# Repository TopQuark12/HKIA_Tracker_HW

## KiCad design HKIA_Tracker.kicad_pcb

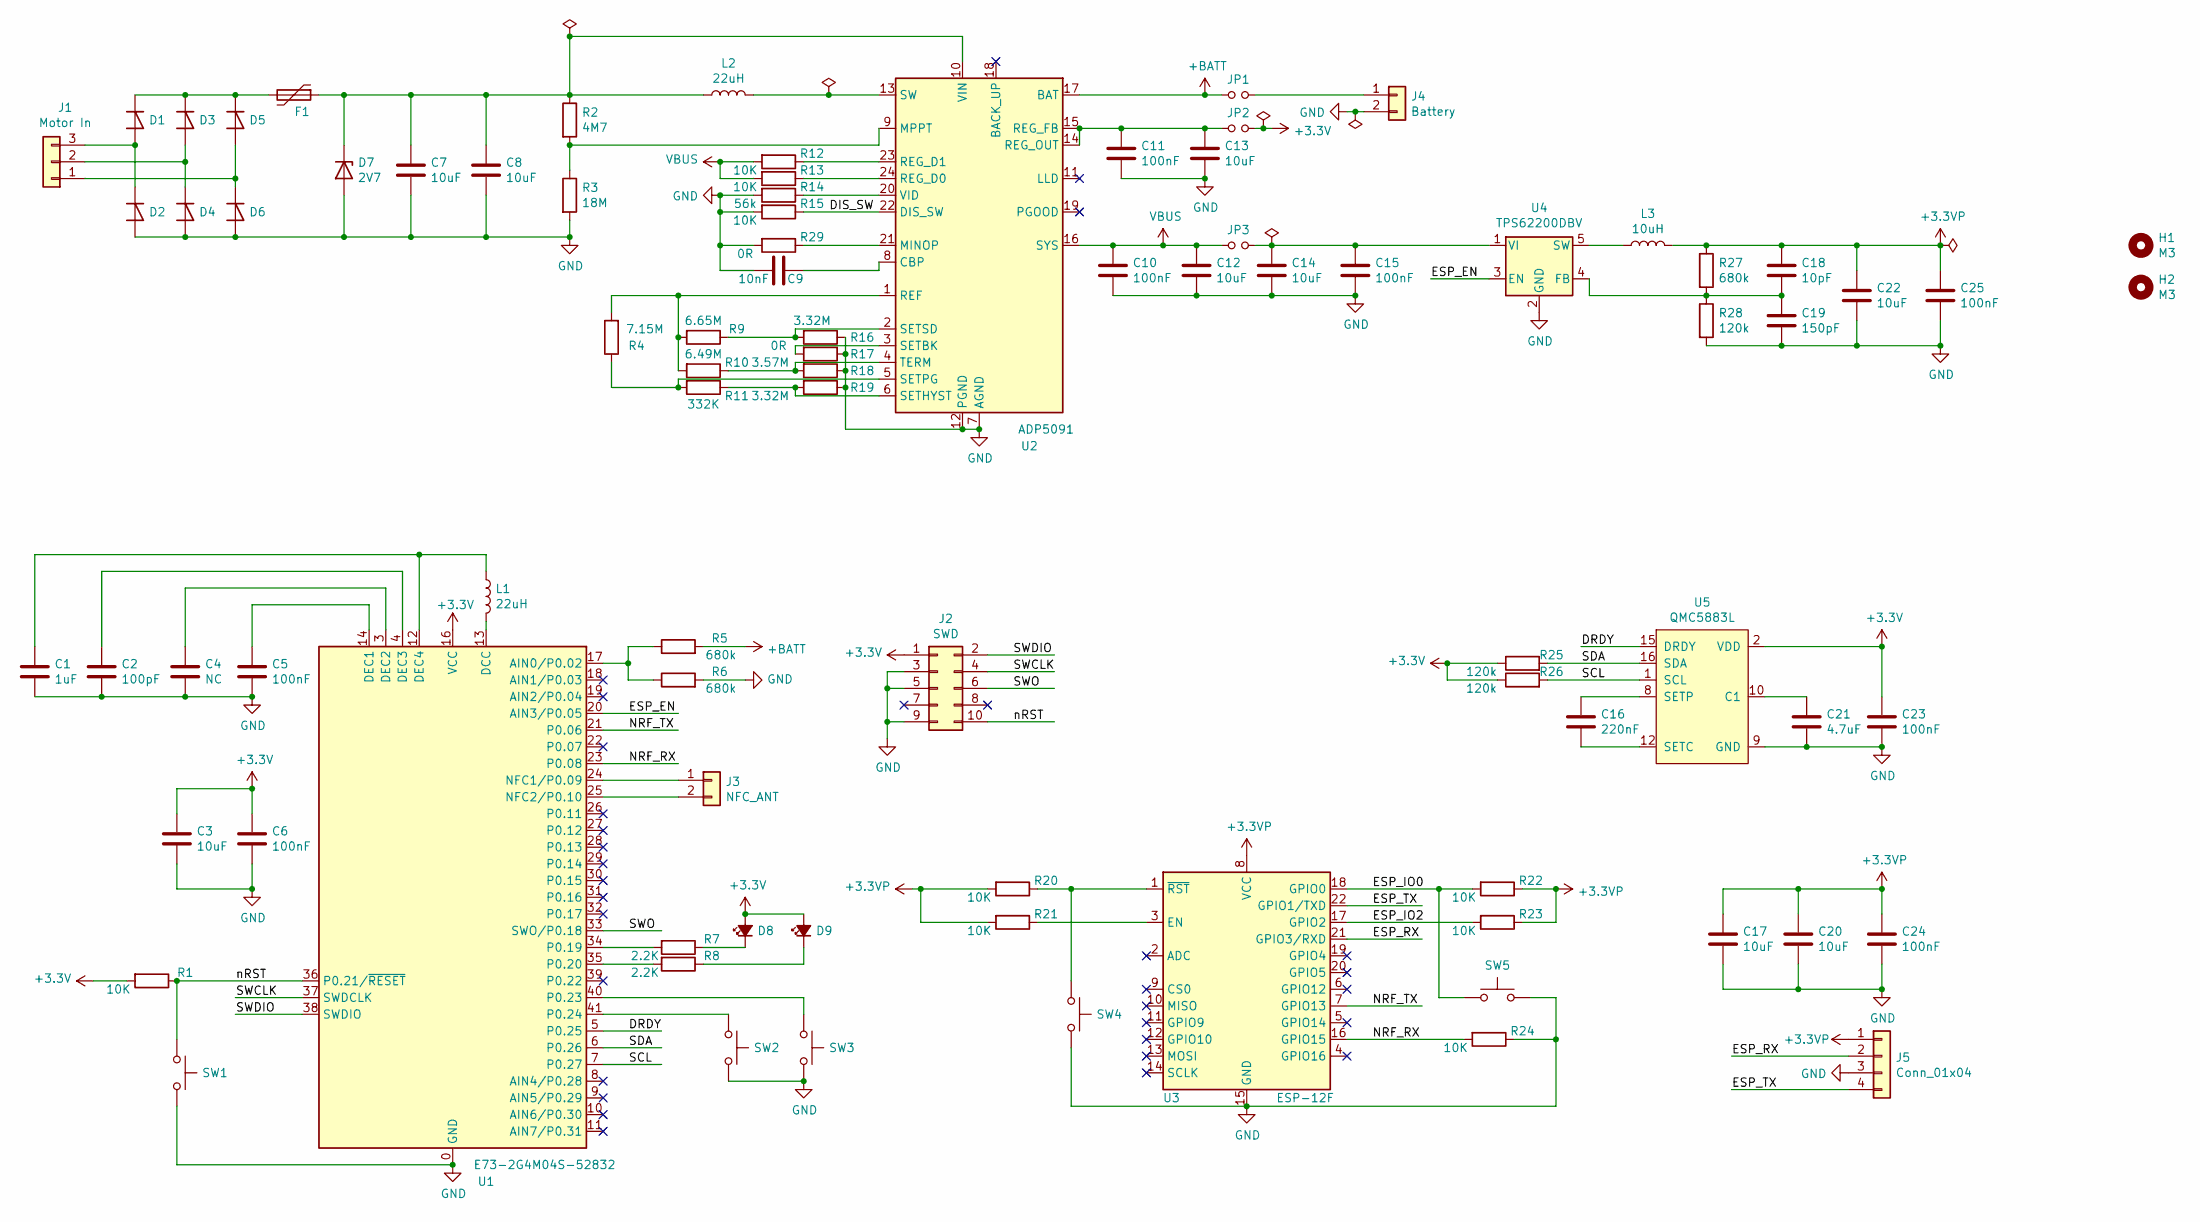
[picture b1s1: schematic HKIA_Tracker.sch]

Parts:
C1: 1uF; C_0603_1608Metric; LCSC C105174
C2: 100pF; C_0603_1608Metric; LCSC C14665
C3, C7, C8, C12, C13, C14, C17, C20, C22: 10uF; C_0805_2012Metric; LCSC C95841
C4: NC; C_0603_1608Metric
C5, C6, C10, C11, C15, C23, C24, C25: 100nF; C_0603_1608Metric; LCSC C1591
C9: 10nF; C_0603_1608Metric; LCSC C76710
C16: 220nF; C_0603_1608Metric; LCSC C83626
C18: 10pF; C_0603_1608Metric; LCSC C106245
C19: 150pF; C_0603_1608Metric; LCSC C107038
C21: 4.7uF; C_0603_1608Metric; LCSC C108342
D1, D2, D3, D4, D5, D6: 15MQ060N; D_SMA; LCSC C260222
D7: 2V7; SOT-223; DIGI 1727-5570-1-ND
D8, D9: LED_Small_ALT; D_0603_1608Metric; LCSC C72043
F1: MF-NSMF035X-2; R_1206_3216Metric; LCSC C208468
H1, H2: M3; MountingHole_3.2mm_M3_Pad
J1: Motor In; PinHeader_1x03_P2.54mm_Vertical
J2: SWD; PinHeader_2x05_P1.27mm_Vertical_SMD
J3: NFC_ANT; PinHeader_1x02_P2.54mm_Vertical
J4: Battery; JST_PH_S2B-PH-SM4-TB_1x02-1MP_P2.00mm_Horizontal; LCSC C132500
J5: Conn_01x04; PinHeader_1x04_P2.54mm_Vertical
JP1, JP2, JP3: Jumper_NO_Small; SolderJumper-2_P1.3mm_Open_RoundedPad1.0x1.5mm
L1, L2: 22uH; L_1210_3225Metric; LCSC C223225
L3: 10uH; L_1210_3225Metric; LCSC C21764
R1, R12, R13, R15, R20, R21, R22, R23, R24: 10K; R_0603_1608Metric; LCSC C98220
R2: 4M7; R_0603_1608Metric; LCSC C170740
R3: 18M; R_0603_1608Metric; LCSC C407494
R4: 7.15M; R_0603_1608Metric; LCSC C482906
R5, R6, R27: 680k; R_0603_1608Metric; LCSC C25822
R7, R8: 2.2K; R_0603_1608Metric; LCSC C25992
R9: 6.65M; R_0603_1608Metric; LCSC C228029
R10: 6.49M; R_0603_1608Metric; LCSC C482895
R11: 332K; R_0603_1608Metric; LCSC C23139
R14: 56k; R_0603_1608Metric; LCSC C304766
R16, R19: 3.32M; R_0603_1608Metric; LCSC C422938
R17, R29: 0R; R_0603_1608Metric; LCSC C15402
R18: 3.57M; R_0603_1608Metric; LCSC C367747
R25, R26, R28: 120k; R_0603_1608Metric; LCSC C203266
SW1, SW2, SW3, SW4, SW5: SW_Push; SW_SPST_CK_KXT3; LCSC C221821
U1: E73-2G4M04S-52832; E73-2G4M04S
U2: ADP5091; LFCSP-24-1EP_4x4mm_P0.5mm_EP2.3x2.3mm
U3: ESP-12F; ESP-12E
U4: TPS62200DBV; SOT-23-5
U5: QMC5883L; LGA-16_3x3mm_P0.5mm

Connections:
+3.3VP: C17.1, C18.1, C20.1, C22.1, C24.1, C25.1, J5.1, L3.2, R20.2, R21.2, R22.1, R23.1, R27.1, U3.8 (VCC)
+3V3: C3.1, C6.1, C23.1, D8.2 (A), D9.2 (A), J2.1, JP2.2, R1.2, R25.1, R26.1, U1.16 (VCC), U5.2 (VDD), U5.4 (S1), U5.13 (VDDIO)
+BATT: JP1.1, R5.2, U2.17 (BAT)
/DIS_SW: R15.1, U2.22 (DIS_SW)
/DRDY: U1.5 (P0.25), U5.15 (DRDY)
/ESP_EN: U1.20 (AIN3/P0.05), U4.3 (EN)
/ESP_IO0: R22.2, SW5.1, U3.18 (GPIO0)
/ESP_IO2: R23.2, U3.17 (GPIO2)
/ESP_RX: J5.2, U3.21 (GPIO3/RXD)
/ESP_TX: J5.4, U3.22 (GPIO1/TXD)
/NRF_RX: R24.2, U1.23 (P0.08), U3.16 (GPIO15)
/NRF_TX: U1.21 (P0.06), U3.7 (GPIO13)
/SCL: R26.2, U1.7 (P0.27), U5.1 (SCL)
/SDA: R25.2, U1.6 (P0.26), U5.16 (SDA)
/SWCLK: J2.4, U1.37 (SWDCLK)
/SWDIO: J2.2, U1.38 (SWDIO)
/SWO: J2.6, U1.33 (SWO/P0.18)
/nRST: J2.10, R1.1, SW1.1, U1.36 (P0.21/~RESET)
GND: C1.1, C2.2, C3.2, C4.2, C5.2, C6.2, C7.2, C8.2, C9.2, C10.2, C11.2, C12.2, C13.2, C14.2, C15.2, C17.2, C19.2, C20.2, C21.2, C22.2, C23.2, C24.2, C25.2, D2.2 (A), D4.2 (A), D6.2 (A), D7.1 (A), D7.3 (A), J2.3, J2.5, J2.9, J4.2, J4.MP, J5.3, R3.2, R6.2, R14.2, R15.2, R16.1, R17.1, R18.1, R19.1, R24.1, R28.2, R29.2, SW1.2, SW2.2, SW3.2, SW4.2, SW5.2, U1.0 (GND), U1.1 (GND), U1.2 (GND), U1.15 (GND), U1.42 (GND), U1.43 (GND), U2.7 (AGND), U2.12 (PGND), U2.25 (AGND), U3.15 (GND), U4.2 (GND), U5.9 (GND), U5.11 (GND)
unnamed: C1.2, L1.1, U1.12 (DEC4)
unnamed: C2.1, U1.4 (DEC3)
unnamed: C4.1, U1.3 (DEC2)
unnamed: C5.1, U1.14 (DEC1)
unnamed: C7.1, C8.1, D7.2 (K), D7.4 (K), F1.1, L2.1, R2.1, U2.10 (VIN)
unnamed: C9.1, U2.8 (CBP)
unnamed: C11.1, C13.1, JP2.1, U2.14 (REG_OUT), U2.15 (REG_FB)
unnamed: C14.1, C15.1, JP3.2, U4.1 (VI)
unnamed: C16.1, U5.8 (SETP)
unnamed: C16.2, U5.12 (SETC)
unnamed: C18.2, C19.1, R27.2, R28.1, U4.4 (FB)
unnamed: C21.1, U5.10 (C1)
unnamed: D1.1 (K), D3.1 (K), D5.1 (K), F1.2
unnamed: D1.2 (A), D2.1 (K), J1.3
unnamed: D3.2 (A), D4.1 (K), J1.2
unnamed: D5.2 (A), D6.1 (K), J1.1
unnamed: D8.1 (K), R7.1
unnamed: D9.1 (K), R8.1
unnamed: J3.1, U1.24 (NFC1/P0.09)
unnamed: J3.2, U1.25 (NFC2/P0.10)
unnamed: J4.1, JP1.2
unnamed: L1.2, U1.13 (DCC)
unnamed: L2.2, U2.13 (SW)
unnamed: L3.1, U4.5 (SW)
unnamed: R2.2, R3.1, U2.9 (MPPT)
unnamed: R5.1, R6.1, U1.17 (AIN0/P0.02)
unnamed: R7.2, U1.34 (P0.19)
unnamed: R8.2, U1.35 (P0.20)
unnamed: R10.1, R18.2, U2.4 (TERM)
unnamed: R4.2, R9.2, R10.2, U2.1 (REF)
unnamed: R11.1, R19.2, U2.6 (SETHYST)
unnamed: R4.1, R11.2, U2.5 (SETPG)
unnamed: R12.1, U2.23 (REG_D1)
unnamed: R13.1, U2.24 (REG_D0)
unnamed: R14.1, U2.20 (VID)
unnamed: R9.1, R16.2, U2.2 (SETSD)
unnamed: R17.2, U2.3 (SETBK)
unnamed: R20.1, SW4.1, U3.1 (~RST)
unnamed: R21.1, U3.3 (EN)
unnamed: R29.1, U2.21 (MINOP)
unnamed: SW2.1, U1.41 (P0.24)
unnamed: SW3.1, U1.40 (P0.23)
VBUS: C10.1, C12.1, JP3.1, R12.2, R13.2, U2.16 (SYS)

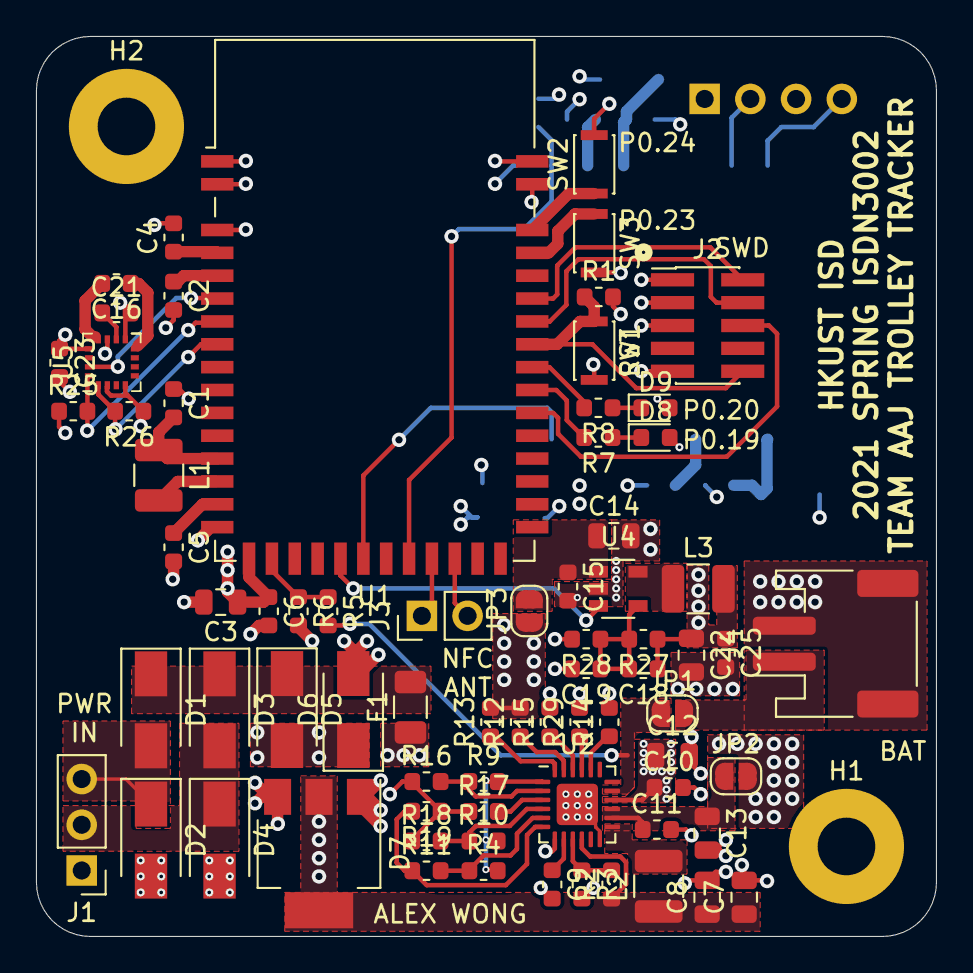
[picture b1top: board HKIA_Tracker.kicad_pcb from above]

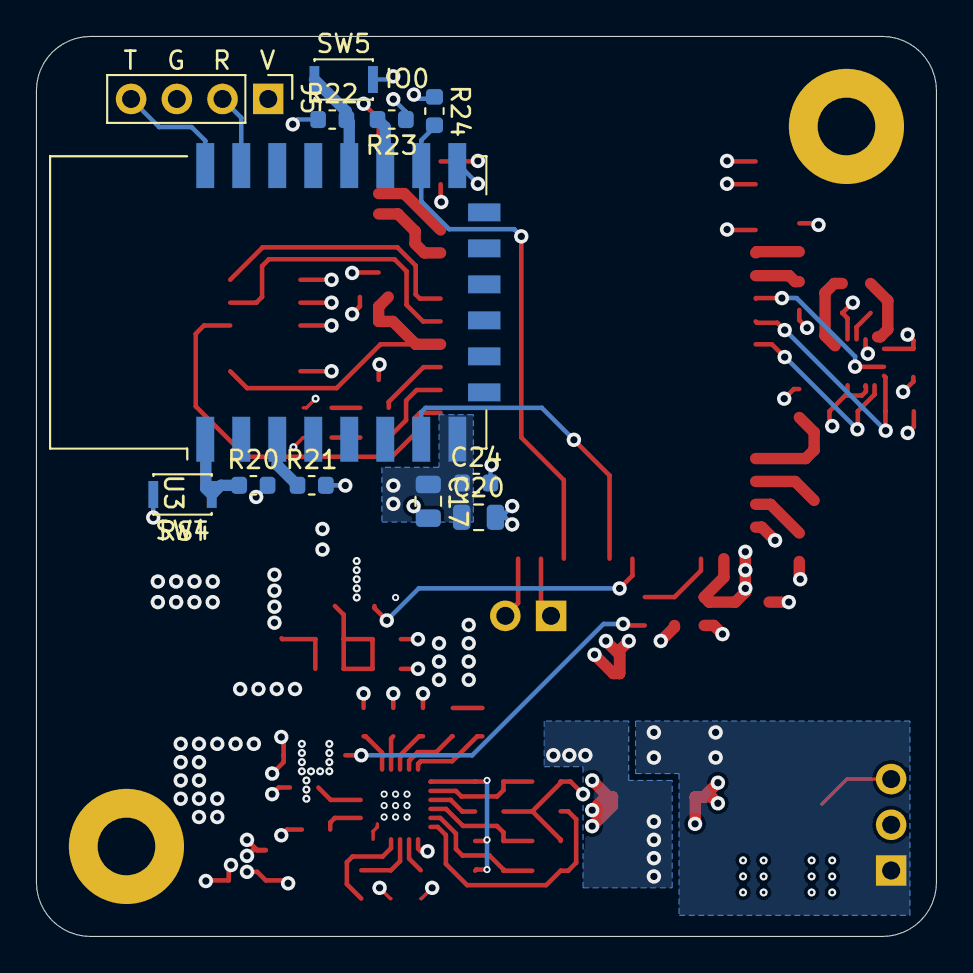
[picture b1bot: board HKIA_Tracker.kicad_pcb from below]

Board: 4 copper layers, 50.0 x 50.0 mm, 87 parts (12 on the bottom side), 62 nets.

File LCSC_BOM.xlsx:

Item | Qty | Reference(s) | Value | LibPart | Footprint | Datasheet | DIGI | LCSC | SKU
1 | 1 | C1 | 1uF | Device:C | Capacitor_SMD:C_0603_1608Metric | ~ |  | C105174
2 | 1 | C2 | 100pF | Device:C | Capacitor_SMD:C_0603_1608Metric | ~ |  | C14665
3 | 9 | C3, C7, C8, C12, C13, C14, C17, C20, C22 | 10uF | Device:C | Capacitor_SMD:C_0805_2012Metric | ~ |  | C95841 | CL21B106KOQNNNE
4 | 1 | C4 | NC | Device:C | Capacitor_SMD:C_0603_1608Metric | ~
5 | 8 | C5, C6, C10, C11, C15, C23, C24, C25 | 100nF | Device:C | Capacitor_SMD:C_0603_1608Metric | ~ |  | C1591 | CL21B106KOQNNNE
6 | 1 | C9 | 10nF | Device:C | Capacitor_SMD:C_0603_1608Metric | ~ |  | C76710
7 | 1 | C16 | 220nF | Device:C | Capacitor_SMD:C_0603_1608Metric | ~ |  | C83626
8 | 1 | C18 | 10pF | Device:C | Capacitor_SMD:C_0603_1608Metric | ~ |  | C106245
9 | 1 | C19 | 150pF | Device:C | Capacitor_SMD:C_0603_1608Metric | ~ |  | C107038
10 | 1 | C21 | 4.7uF | Device:C | Capacitor_SMD:C_0603_1608Metric | ~ |  | C108342
11 | 6 | D1, D2, D3, D4, D5, D6 | 15MQ060N | Device:D_Shockley | Diode_SMD:D_SMA | https://datasheet.lcsc.com/lcsc/1811061043_SMC-Sangdest-Micr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 |  | C260222
12 | 1 | D7 | 2V7 | HKIA_Tracker_SYM:D_Zener_BZV90 | Package_TO_SOT_SMD:SOT-223 | ~ | 1727-5570-1-ND
13 | 2 | D8, D9 | LED_Small_ALT | Device:LED_Small_ALT | Diode_SMD:D_0603_1608Metric | ~ |  | C72043
14 | 1 | F1 | MF-NSMF035X-2 | Device:Polyfuse | Resistor_SMD:R_1206_3216Metric | https://datasheet.lcsc.com/lcsc/BOURNS-MF-NSMF035X-2_C208468.pdf |  | C208468
15 | 2 | H1, H2 | M3 | Mechanical:MountingHole | MountingHole:MountingHole_3.2mm_M3_Pad | ~
16 | 1 | J1 | Motor In | Connector_Generic:Conn_01x03 | Connector_PinHeader_2.54mm:PinHeader_1x03_P2.54mm_Vertical | ~
17 | 1 | J2 | SWD | Connector_Generic:Conn_02x05_Odd_Even | Connector_PinHeader_1.27mm:PinHeader_2x05_P1.27mm_Vertical_SMD | ~
18 | 1 | J3 | NFC_ANT | Connector_Generic:Conn_01x02 | Connector_PinHeader_2.54mm:PinHeader_1x02_P2.54mm_Vertical | ~
19 | 1 | J4 | Battery | Connector_Generic:Conn_01x02 | Connector_JST:JST_PH_S2B-PH-SM4-TB_1x02-1MP_P2.00mm_Horizontal | ~ |  | C132500
20 | 1 | J5 | Conn_01x04 | Connector_Generic:Conn_01x04 | Connector_PinHeader_2.54mm:PinHeader_1x04_P2.54mm_Vertical | ~
21 | 3 | JP1, JP2, JP3 | Jumper_NO_Small | Device:Jumper_NO_Small | Jumper:SolderJumper-2_P1.3mm_Open_RoundedPad1.0x1.5mm | ~
22 | 2 | L1, L2 | 22uH | Device:L | Inductor_SMD:L_1210_3225Metric | https://datasheet.lcsc.com/lcsc/1912111437_Taiyo-Yuden-CBC32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 |  | C223225
23 | 1 | L3 | 10uH | Device:L | Inductor_SMD:L_1210_3225Metric | ~ |  | C21764
24 | 9 | R1, R12, R13, R15, R20, R21, R22, R23, R24 | 10K | Device:R | Resistor_SMD:R_0603_1608Metric | ~ |  | C98220
25 | 1 | R2 | 4M7 | Device:R | Resistor_SMD:R_0603_1608Metric | ~ |  | C170740
26 | 1 | R3 | 18M | Device:R | Resistor_SMD:R_0603_1608Metric | ~ |  | C407494
27 | 1 | R4 | 7.15M | Device:R | Resistor_SMD:R_0603_1608Metric | ~ |  | C482906
28 | 3 | R5, R6, R27 | 680k | Device:R | Resistor_SMD:R_0603_1608Metric | ~ |  | C25822
29 | 2 | R7, R8 | 2.2K | Device:R | Resistor_SMD:R_0603_1608Metric | ~ |  | C25992
30 | 1 | R9 | 6.65M | Device:R | Resistor_SMD:R_0603_1608Metric | ~ |  | C228029
31 | 1 | R10 | 6.49M | Device:R | Resistor_SMD:R_0603_1608Metric | ~ |  | C482895
32 | 1 | R11 | 332K | Device:R | Resistor_SMD:R_0603_1608Metric | ~ |  | C23139
33 | 1 | R14 | 56k | Device:R | Resistor_SMD:R_0603_1608Metric | ~ |  | C304766
34 | 2 | R16, R19 | 3.32M | Device:R | Resistor_SMD:R_0603_1608Metric | ~ |  | C422938
35 | 2 | R17, R29 | 0R | Device:R | Resistor_SMD:R_0603_1608Metric | ~ |  | C15402
36 | 1 | R18 | 3.57M | Device:R | Resistor_SMD:R_0603_1608Metric | ~ |  | C367747
37 | 3 | R25, R26, R28 | 120k | Device:R | Resistor_SMD:R_0603_1608Metric | ~ |  | C203266
38 | 5 | SW1, SW2, SW3, SW4, SW5 | SW_Push | Switch:SW_Push | Button_Switch_SMD:SW_SPST_CK_KXT3 | ~ |  | C221821
39 | 1 | U1 | E73-2G4M04S-52832 | RF_Module:E73-2G4M04S-52832 | RF_Module:E73-2G4M04S | http://www.cdebyte.com/en/downpdf.aspx?id=243
40 | 1 | U2 | ADP5091 | Battery_Management:ADP5091 | Package_CSP:LFCSP-24-1EP_4x4mm_P0.5mm_EP2.3x2.3mm | https://www.analog.com/media/en/technical-documentation/data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
41 | 1 | U3 | ESP-12F | RF_Module:ESP-12F | RF_Module:ESP-12E | http://wiki.ai-thinker.com/_media/esp8266/esp8266_series_mod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
42 | 1 | U4 | TPS62200DBV | Regulator_Switching:TPS62200DBV | Package_TO_SOT_SMD:SOT-23-5 | http://www.ti.com/lit/ds/symlink/tps62201.pdf
43 | 1 | U5 | QMC5883L | HKIA_Tracker_SYM:QMC5883L | Package_LGA:LGA-16_3x3mm_P0.5mm | https://datasheet.lcsc.com/lcsc/QST-QMC5883L-TR_C192585.pdf

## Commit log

2021-05-17 create project
2021-05-19 ADP done
2021-05-21 sch done
2021-05-21 add button and led
2021-05-21 fix issues
2021-05-21 added power jumpers
2021-05-21 save
2021-05-21 init placement
2021-05-22 done
2021-05-22 added bom
2021-05-22 Release
2021-05-22 add screenshots
2021-05-22 add sch in pdf
